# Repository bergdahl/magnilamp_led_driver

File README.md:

# magnilamp_led_driver

This is a modification of the Velleman _VTLLAMP1W_ 6W LEDmagnifying glass lamp - https://www.velleman.eu/products/view/?id=380108. 
The modification should also be possible with the 10W successor _WTLLAMP1WN_. 

> Please start this project by cutting off the mains plug so you can't accidently plug it into mains again!

It is powered by 12V and uses a constant current LED driver to drive 24 1W LED's placed on 8 aluminium PCB's.

Gerber files for the PCB's can be found in the Gerber folder, design files for EAGLE can be found in the pcb folder, and design files for Fusion360 for the optional mounting ring can be found in the cad folder.

# LED driver board

The LED driver is based on the XLSEMI XL6013 Boost LED driver. 

# LED board

The LED boards are designed to be drop-in replacement of the orginal LED boards.

# Mounting hardware

I designed a replacement 3D printable mounting ring. If you don't have a 3D printer, you can instead modify the original, and make cutouts for the new LED lighting. 

I tried to use PETG, but it turned out to be too brittle so I ended out printing it in clear PLA instead. Also, I really hate the stringing PETG. In the end it turned out the lamp does not get hot, so PLA is perfectly fine for this.

# Assembly

I am reusing the 240V cable for power, using blue for 12V and brown for GND. I used double sided tape to fasten the LED driver in the lamp. 

The LED PCB's should be soldered together 2 by 2, and the resulting 2 LED "strips" soldered to the LED board.

Finish up by connecting the old mains wires to 12V and GND of the LED driver. 

# Final product.

I actually had to lower the current to the LED's as it was way to bright. I run it at 15W now instead of 24W and my lux meter tells me it outputs 7000 lux. That is plenty bright, and the life time of the LED's will be almost infinite.

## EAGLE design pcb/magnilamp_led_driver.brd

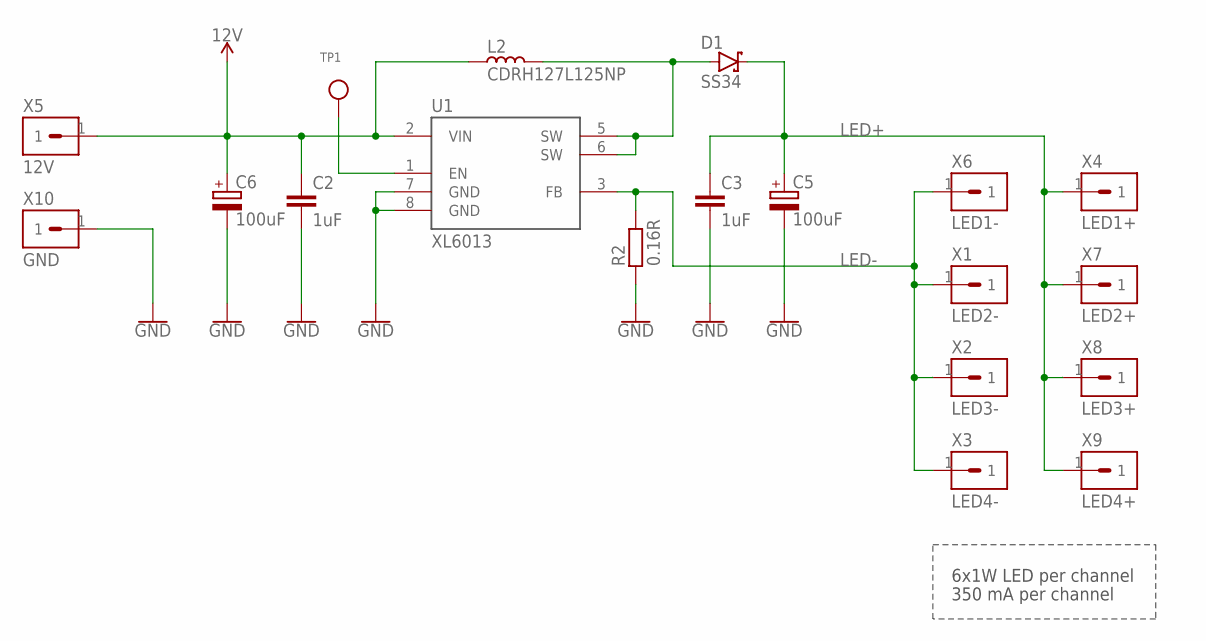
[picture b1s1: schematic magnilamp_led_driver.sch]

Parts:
C2, C3: 1uF; C0603
C5, C6: 100uF; KEMET-KN
D1: SS34; DO-214AC
L2: CDRH127L125NP; SUMIDA-CDRH127L125
R2: 0.16R; R1206
TP1: TESTPOINTPAD; TESTPOINT_PAD_2MM
U1: XL6013; SOP8
X1: LED2-; SOLDERPAD-4X5
X2: LED3-; SOLDERPAD-4X5
X3: LED4-; SOLDERPAD-4X5
X4: LED1+; SOLDERPAD-4X5
X5: 12V; SOLDERPAD-4X5
X6: LED1-; SOLDERPAD-4X5
X7: LED2+; SOLDERPAD-4X5
X8: LED3+; SOLDERPAD-4X5
X9: LED4+; SOLDERPAD-4X5
X10: GND; SOLDERPAD-4X5

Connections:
12V: C2.1, C6.+, L2.1, U1.2 (VIN), X5.1
GND: C2.2, C3.2, C5.-, C6.-, R2.1, U1.7 (GND), U1.8 (GND), X10.1
LED+: C3.1, C5.+, D1.C, X4.1, X7.1, X8.1, X9.1
LED-: R2.2, U1.3 (FB), X1.1, X2.1, X3.1, X6.1
unnamed: TP1.P$1, U1.1 (EN)
unnamed: D1.A, L2.2, U1.5 (SW), U1.6 (SW)

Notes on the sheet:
6x1W LED per channel
350 mA per channel

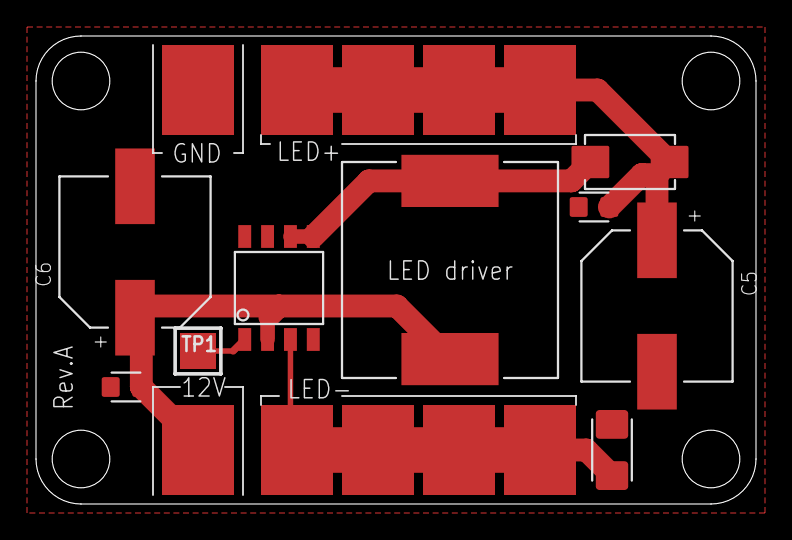
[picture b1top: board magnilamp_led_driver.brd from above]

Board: 2 copper layers, 40.0 x 26.0 mm, 19 parts (0 on the bottom side), 6 nets.

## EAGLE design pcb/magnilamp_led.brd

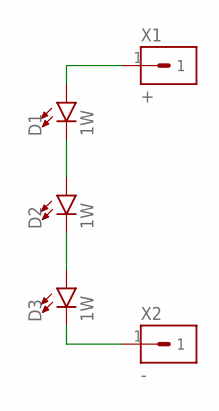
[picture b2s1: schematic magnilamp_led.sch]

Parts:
D1, D2, D3: 1W; LED_1W
X1: +; SOLDERPAD-4X5
X2: -; SOLDERPAD-4X5

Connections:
unnamed: D1.A, X1.1
unnamed: D1.C, D2.A
unnamed: D2.C, D3.A
unnamed: D3.C, X2.1

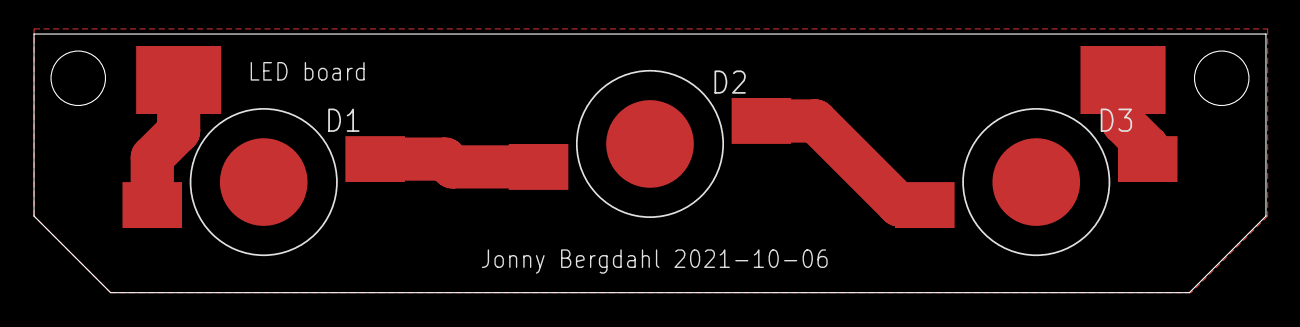
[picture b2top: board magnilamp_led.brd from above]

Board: 2 copper layers, 72.4 x 15.2 mm, 5 parts (0 on the bottom side), 4 nets.

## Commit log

2021-10-23 Added documentation
2021-10-23 Added schematics
2021-10-23 Added info for the lamp.
